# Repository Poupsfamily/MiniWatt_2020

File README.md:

# MiniWatt_2020
MiniWatt UPGRADE

## Cahier des charges ELECTRONIQUE MINIWATT 2020 

Actuellement sur Minilitre :
 
 Carte moteur V5 : version 01 sans coupure TRACCO (1J/s) / version 02 avec coupure
TRACCO (0,5J/s). 
 Carte puissance : TRACCO 36V to 12V pour le klaxon / Relais OMRON général arrêt
d’urgence 36V-16A. 
Carte BMS 1S to 13S.
Carte adaptation BMS 10S pour équilibrage des batteries sur le proto pendant la course.
Carte interface RASPI.
RASPI : pilotage du crabot, gestion du chrono course, du nombre de tours, coupure vitesse, 
affichage vitesse proto.
Klaxon 12V-1,5A-105dB avec relais automobile 12V-20A + relais automobile 12V-30A situé 
juste à côté.
Batterie Lipo 10S-4000mAh (2 x 5S en série sous 1 pack). 

A prévoir sur MiniWatt :
 
 Enlever :
 RASPI.
 Carte interface RASPI.
 Carte de puissance.
 Kaxon 12V.
 Batterie lipo 10S-4000mAh.
 Carte d’adaptation BMS 10S. 

 Carte générale avec à y intégrer : 
 La carte moteur V5 à modifier avec coupure du TRACCO (possible de la
supprimer avec un shunt) + enlever l’optocoupleur ON/OFF moteur par le
RASPI et remplacer la commande ON/OFF par une simple commande par
interrupteur (pull down) + mettre driver de MOS sur support + passer le max
de composants en CMS + fixer mécaniquement les radiateurs pour éviter de
tirer sur les soudures des MOS + souder les MOS de type CMS. 
 Le relais OMRON général arrêt d’urgence à modifier en 48V-16A.
 Le relais klaxon OMRON 48V- ?? A (à choisir).
 1 ou 2 embase(s) RJ45 pour liaison avec les commandes poste de pilotage.
 1 connecteur pour le klaxon.
 1 connecteur pour la batterie.
 1 connecteur pour le moteur.
 1 système de connexion du joulemètre (possible de shunter pour utilisation 
hors course sans joulemètre) + penser à la position au plus près du moteur et
partie carte moteur. 

 Carte d’adaptation BMS 12S.
 Carte interface RJ45.
 Batterie Lipo 6S-2600mAh (x 2) + cordon Y pour mise en série.
 Klaxon 48V- ?? A-105dB.
 Liaison entre la carte générale et les commandes de pilotage avec un câble RJ45.

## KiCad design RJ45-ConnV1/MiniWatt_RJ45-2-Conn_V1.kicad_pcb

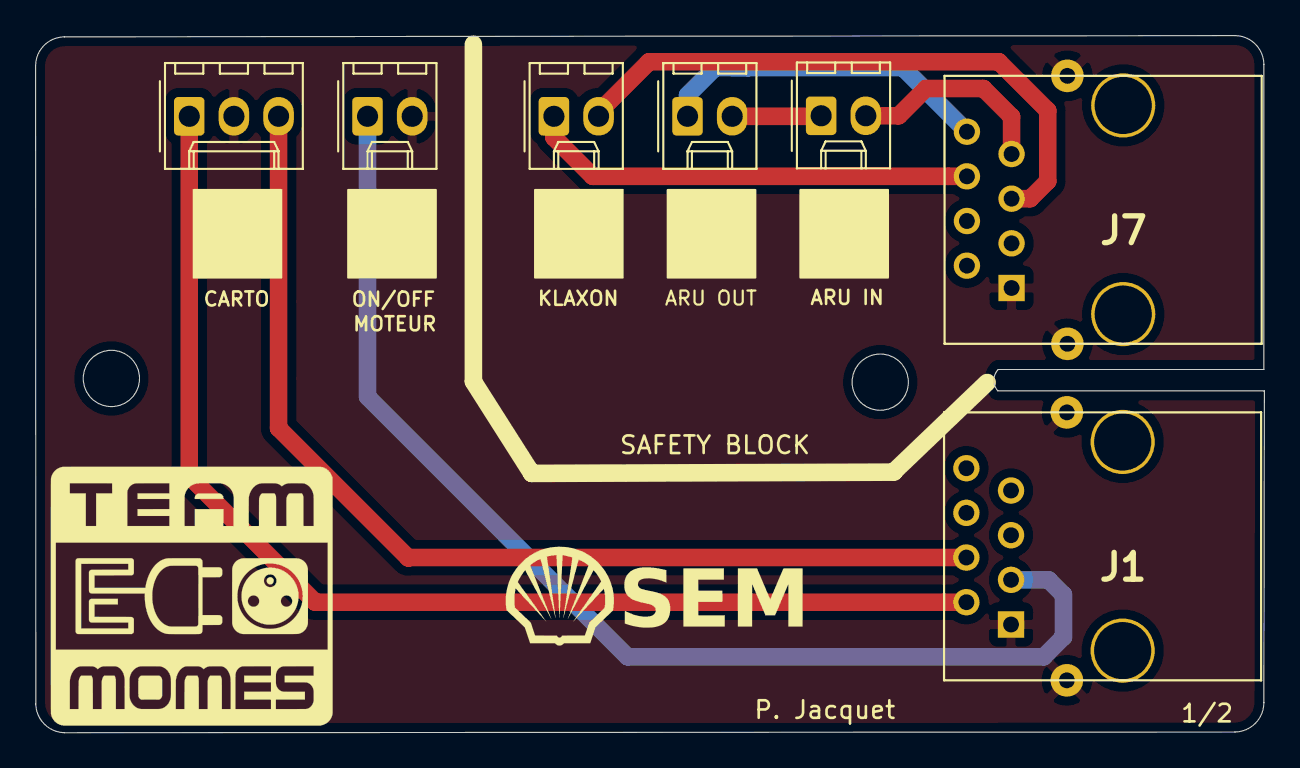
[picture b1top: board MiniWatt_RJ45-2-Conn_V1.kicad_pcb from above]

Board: 2 copper layers, 69.9 x 39.6 mm, 8 parts (0 on the bottom side), 9 nets.

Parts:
ARU IN: Conn_01x02_Female; Molex_KK-254_AE-6410-02A_1x02_P2.54mm_Vertical
ARU OUT: Conn_01x02_Female; Molex_KK-254_AE-6410-02A_1x02_P2.54mm_Vertical
CARTO: Conn_01x03_Female; Molex_KK-254_AE-6410-03A_1x03_P2.54mm_Vertical
J1, J7: RJ45_Shielded_MiniWatt; RJ45_CAN
KLAXON: Conn_01x02_Female; Molex_KK-254_AE-6410-02A_1x02_P2.54mm_Vertical
ON/OFF: Conn_01x02_Female; Molex_KK-254_AE-6410-02A_1x02_P2.54mm_Vertical
VAL: REF; logo_shell2_medium_bottom

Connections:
+5V: CARTO.1, J1.2
ARU: ARU IN.2, J7.7
CARTO_A: CARTO.3, J1.4
GND: CARTO.2, J1.1, J1.9, J7.1, J7.9, ON/OFF.2
GND_ARU: ARU OUT.1, J7.8
GND_KLAXON: J7.6, KLAXON.1
KLAXON: J7.5, KLAXON.2
unnamed: ARU IN.1, ARU OUT.2
ON_OFF: J1.3, ON/OFF.1

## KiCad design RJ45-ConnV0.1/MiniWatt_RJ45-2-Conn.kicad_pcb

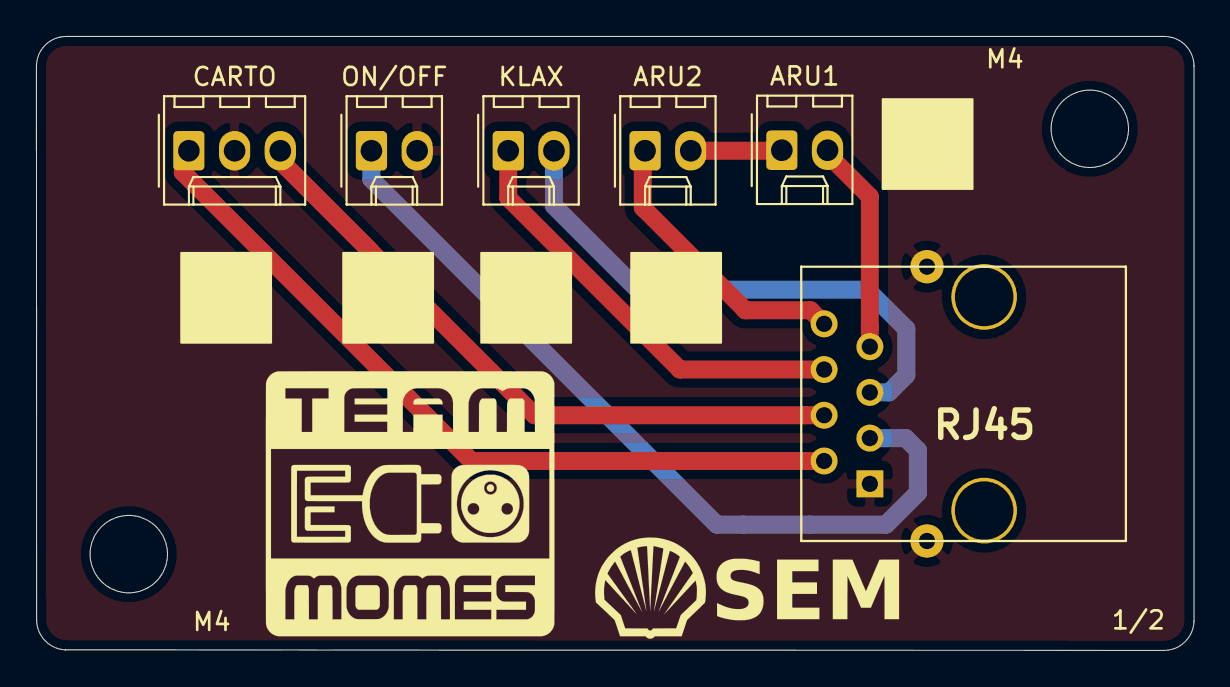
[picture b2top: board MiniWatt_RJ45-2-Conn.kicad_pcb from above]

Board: 2 copper layers, 64.3 x 34.1 mm, 9 parts (0 on the bottom side), 9 nets.

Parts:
ARU1, ARU2: Conn_01x02_Female; Molex_KK-254_AE-6410-02A_1x02_P2.54mm_Vertical
CARTO: Conn_01x03_Female; Molex_KK-254_AE-6410-03A_1x03_P2.54mm_Vertical
KLAX: Conn_01x02_Female; Molex_KK-254_AE-6410-02A_1x02_P2.54mm_Vertical
M4, M4#2: MountingHole_4.3mm_M4
ON/OFF: Conn_01x02_Female; Molex_KK-254_AE-6410-02A_1x02_P2.54mm_Vertical
RJ45: RJ45_Shielded_MiniWatt; RJ45_CAN
VAL: REF; logo_shell2_medium_bottom

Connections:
+5V: CARTO.1, RJ45.2
ARU: ARU1.2, RJ45.7
CARTO_A: CARTO.3, RJ45.4
GND: CARTO.2, ON/OFF.2, RJ45.1, RJ45.9
GND_ARU: ARU2.1, RJ45.8
GND_KLAXON: KLAX.1, RJ45.6
KLAXON: KLAX.2, RJ45.5
unnamed: ARU1.1, ARU2.2
ON_OFF: ON/OFF.1, RJ45.3

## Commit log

2020-02-11 Cahier des charges
    Ajout du cahier des charges fonctionel
2020-02-13 Create BMS adapter
